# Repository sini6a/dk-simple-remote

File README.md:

# DK Simple Remote

A small BLE HID remote built around the WCH CH583, powered by a CR2032 cell.

| Folder / file | Contents |
|---|---|
| [`KiCad/`](KiCad/) | KiCad project `dk-simple-remote`: schematic, PCB, libraries, 3D models |
| `KiCad/production/` | Fabrication outputs (Gerbers, BOM, positions) |
| [`FreeCAD/`](FreeCAD/) | Enclosure |
| `Assets/` | Component datasheets |
| [`Firmware/`](Firmware/README.md) | Firmware source; the WCH SDK is a git submodule |

Clone with the SDK:

```sh
git clone --recurse-submodules <this-repo>
```

## License

This project uses two licenses:

- **Hardware** (everything outside `Firmware/`: the `KiCad/` project,
  fabrication outputs, enclosure and 3D models) is licensed under
  [Creative Commons Attribution-NonCommercial-ShareAlike 4.0](LICENSE)
  (CC BY-NC-SA 4.0). You may build, modify and share it for non-commercial
  purposes with attribution; derivatives must use the same license.
  Selling boards, kits or devices made from this design is not permitted.
- **Firmware** (`Firmware/`) is [MIT licensed](Firmware/LICENSE). WCH SDK
  components and WCH-derived files keep their Apache-2.0 terms; see
  [third-party notices](Firmware/THIRD_PARTY_NOTICES.md).

Datasheets in `Assets/` and vendor 3D models in `KiCad/Models/` belong to their
respective manufacturers and are not covered by either license.

Copyright (c) 2026 CH583 Remote contributors.

## Support

If you find this project useful, you can buy me a coffee:

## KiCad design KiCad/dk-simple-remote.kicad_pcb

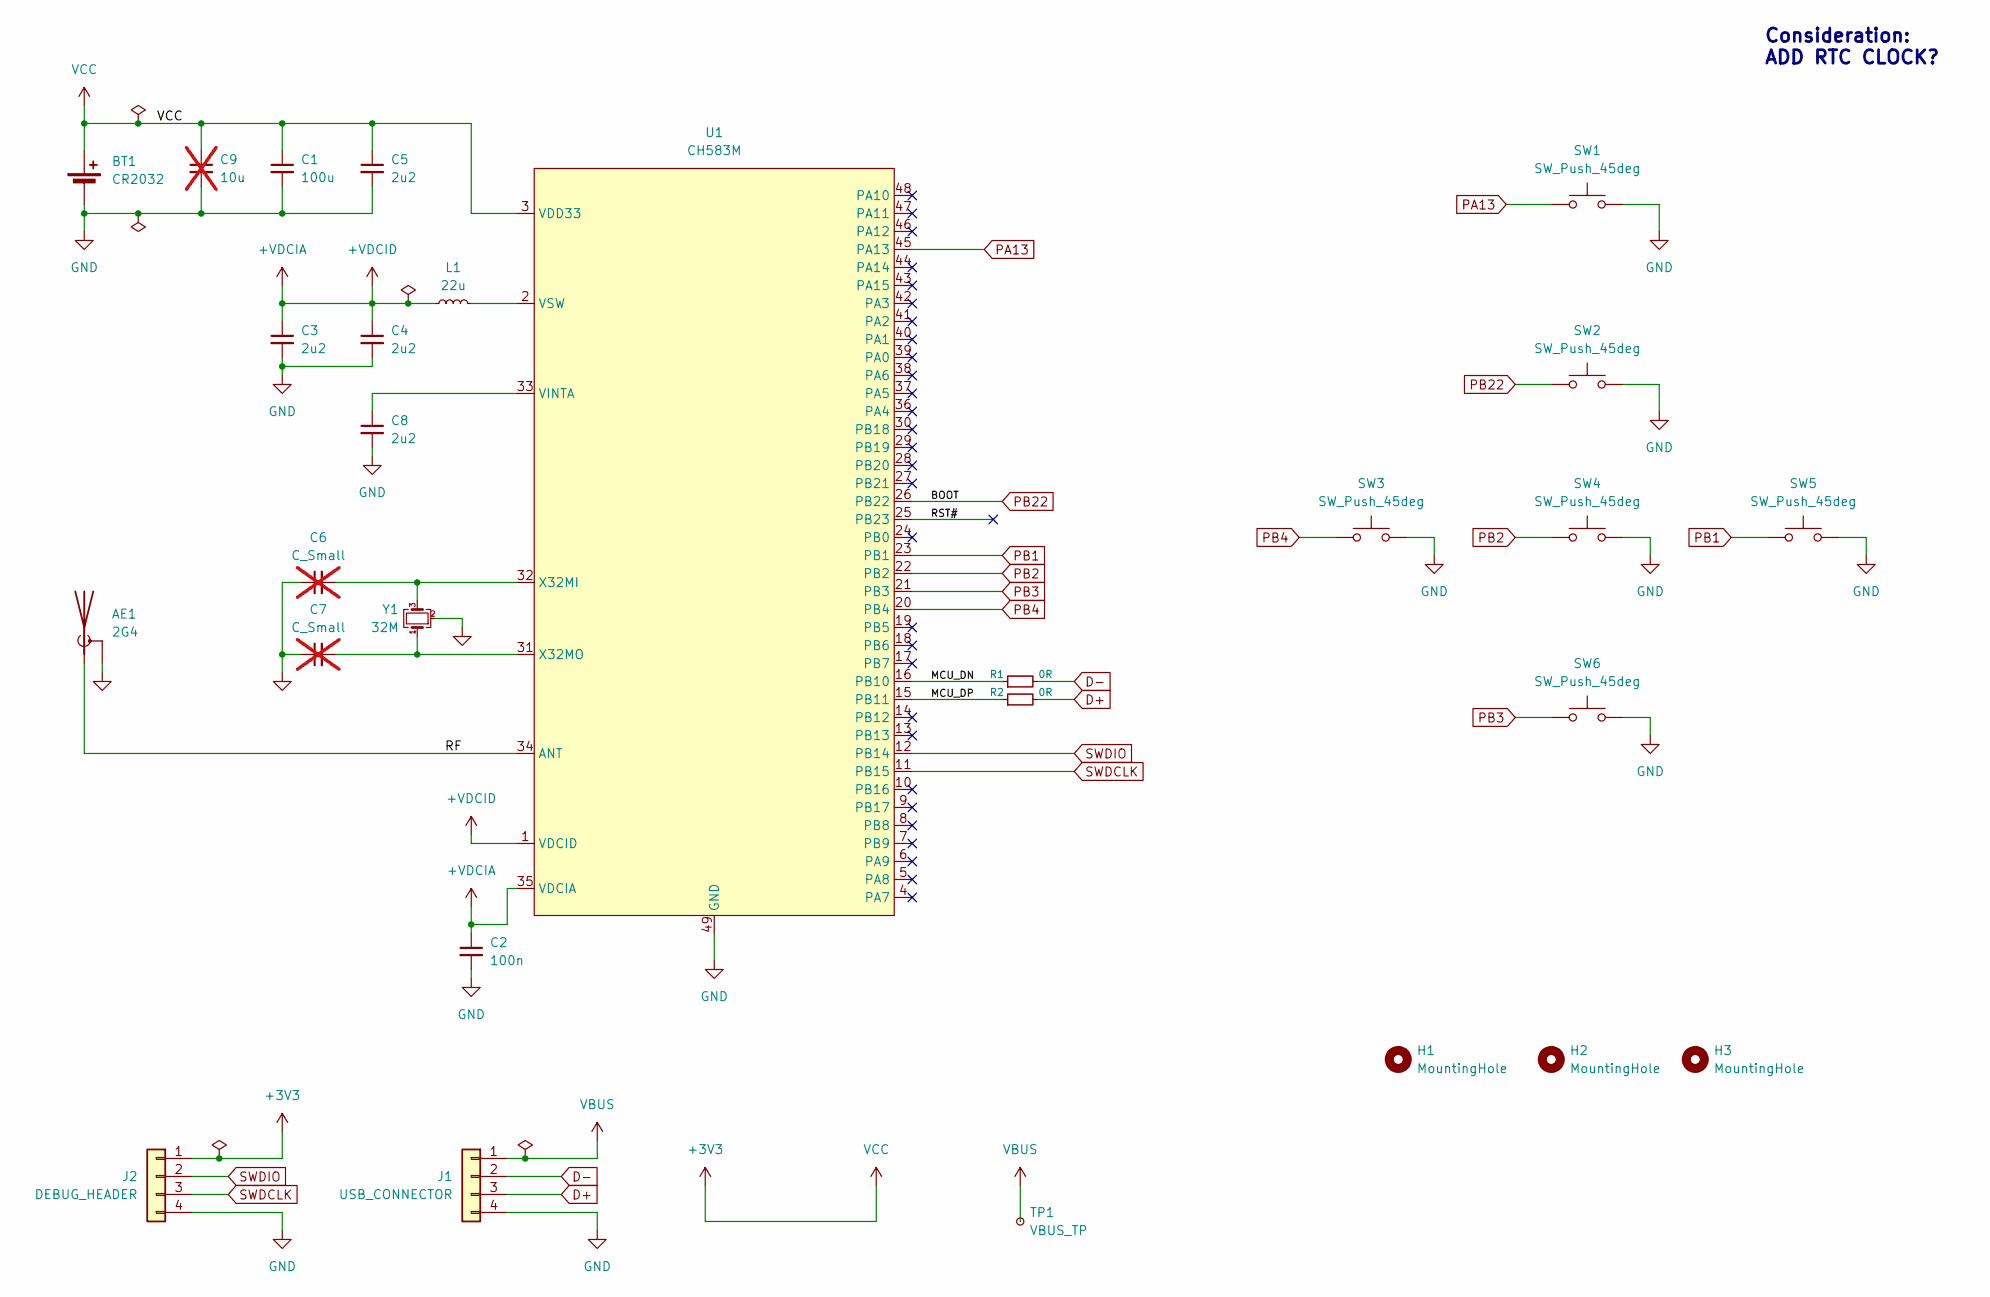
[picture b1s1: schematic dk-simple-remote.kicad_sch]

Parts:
AE1: 2G4; Texas_SWRA117D_2.4GHz_Left
BT1: CR2032; BatteryHolder_MPD_BC2003_1x2032
C1: 100u; C_1206_3216Metric; MPN C15008
C2: 100n; C_0402_1005Metric; MPN C1525
C3, C4, C5, C8: 2u2; C_0402_1005Metric; MPN C12530
C6, C7: C_Small; C_0402_1005Metric; not fitted
C9: 10u; C_0603_1608Metric; MPN C1713; not fitted
H1, H2, H3: MountingHole; MountingHole_3.2mm_M3_ISO14580
J1: USB_CONNECTOR; Hirose_DF13-04P-1.25DSA_1x04_P1.25mm_Vertical
J2: DEBUG_HEADER; Hirose_DF13-04P-1.25DSA_1x04_P1.25mm_Vertical
L1: 22u; L_APV_ANR3010; MPN C6364775
R1, R2: 0R; R_0402_1005Metric; MPN C17168
SW1, SW2, SW3, SW4, SW5, SW6: SW_Push_45deg; SW_Push_1P1T_NO_E-Switch_TL3301NxxxxxG; MPN C2837531
TP1: VBUS_TP; TestPoint_Pad_D1.5mm
U1: CH583M; QFN-48-1EP_5x5mm_P0.35mm_EP3.7x3.7mm
Y1: 32M; Crystal_SMD_2016-4Pin_2.0x1.6mm; MPN C383840

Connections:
+3V3: BT1.1 (+), C1.1, C5.1, C9.1, J2.1, U1.3 (VDD33)
+VDCIA: C2.1, C3.1, C4.1, L1.1, U1.1 (VDCID), U1.35 (VDCIA)
/MCU_DN: R1.1, U1.16 (PB10)
/MCU_DP: R2.1, U1.15 (PB11)
/RF: AE1.1 (A), U1.34 (ANT)
/RST#: U1.25 (PB23)
D+: J1.3, R2.2
D-: J1.2, R1.2
GND: AE1.2 (Shield), BT1.2 (-), C1.2, C2.2, C3.2, C4.2, C5.2, C6.1, C7.1, C8.2, C9.2, J1.4, J2.4, SW1.2, SW2.2, SW3.2, SW4.2, SW5.2, SW6.2, U1.49 (GND), Y1.2 (G), Y1.4 (G)
unnamed: C8.1, U1.33 (VINTA)
unnamed: L1.2, U1.2 (VSW)
unnamed: C6.2, U1.32 (X32MI), Y1.3
unnamed: C7.2, U1.31 (X32MO), Y1.1
PA13: SW1.1, U1.45 (PA13)
PB1: SW5.1, U1.23 (PB1)
PB2: SW4.1, U1.22 (PB2)
PB3: SW6.1, U1.21 (PB3)
PB4: SW3.1, U1.20 (PB4)
PB22: SW2.1, U1.26 (PB22)
SWDCLK: J2.3, U1.11 (PB15)
SWDIO: J2.2, U1.12 (PB14)
VBUS: J1.1, TP1.1 (1_1)

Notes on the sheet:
Consideration: ADD RTC CLOCK?

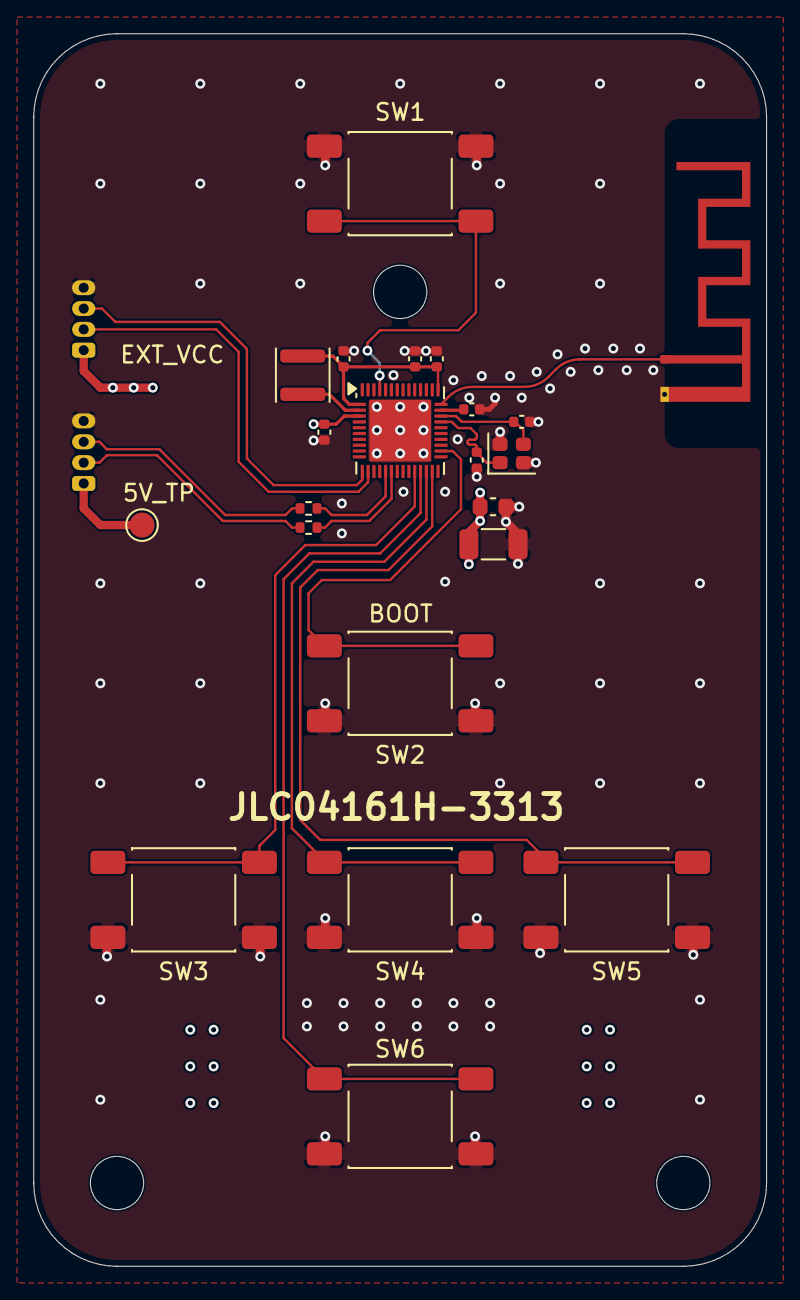
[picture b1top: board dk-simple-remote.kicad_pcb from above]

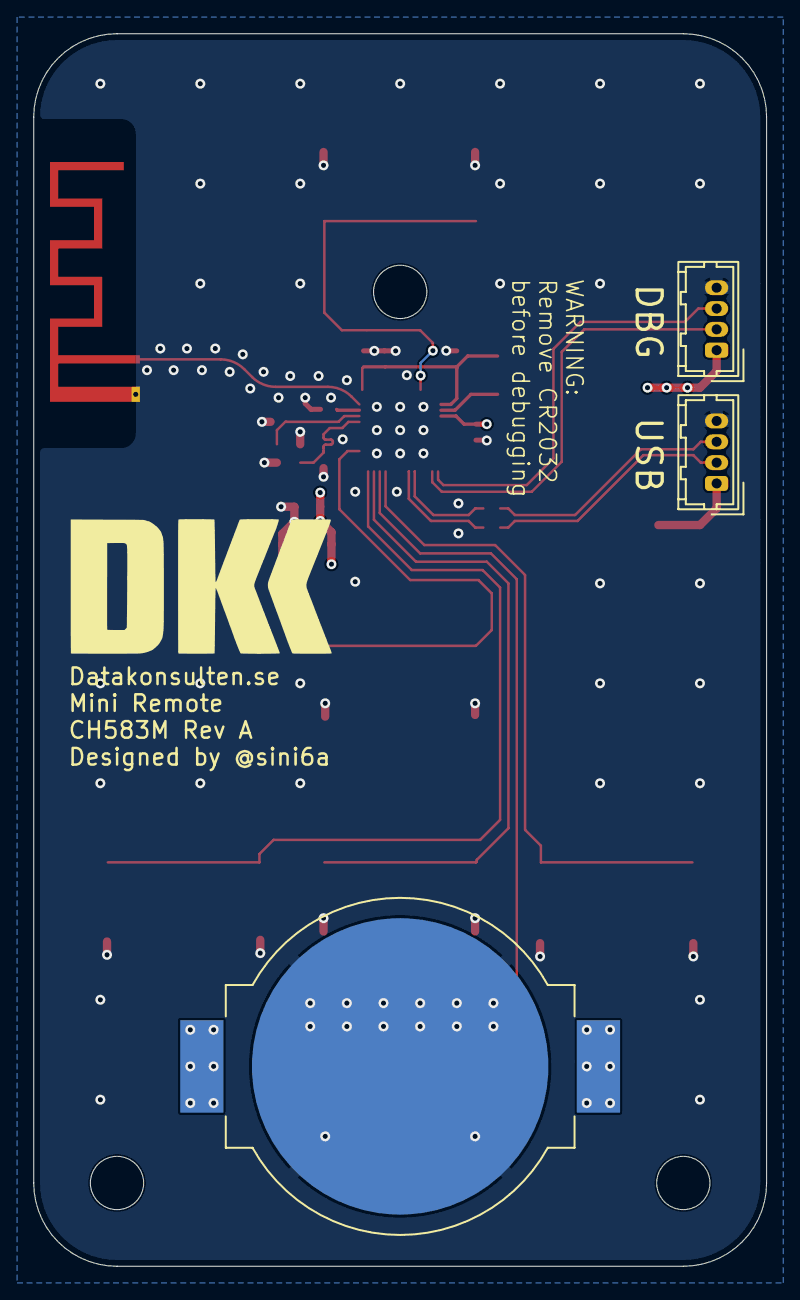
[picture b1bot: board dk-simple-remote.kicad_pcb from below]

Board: 4 copper layers, 44.0 x 74.0 mm, 28 parts (3 on the bottom side), 21 nets.

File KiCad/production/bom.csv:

Designator,Footprint,Quantity,Value,LCSC Part #
BT1,BatteryHolder_MPD_BC2003_1x2032,1,CR2032,
C1,0603,1,10u,C19702
C2,0402,1,100n,C1525
"C3, C4, C5, C8",0402,4,2u2,C12530
J1,Hirose_DF13-04P-1.25DSA_1x04_P1.25mm_Vertical,1,USB_CONNECTOR,
J2,Hirose_DF13-04P-1.25DSA_1x04_P1.25mm_Vertical,1,DEBUG_HEADER,
JP1,SolderJumper-2_P1.3mm_Open_RoundedPad1.0x1.5mm,1,RST#,
JP2,SolderJumper-2_P1.3mm_Open_RoundedPad1.0x1.5mm,1,BOOT,
L1,L_APV_ANR3010,1,22u,C6364775
"R1, R2",0402,2,0R,C17168
"SW1, SW2, SW3, SW4, SW5, SW6",SW_Push_1P1T_NO_E-Switch_TL3301NxxxxxG,6,SW_Push_45deg,C2837531
TP1,TestPoint_Pad_D1.5mm,1,VBUS_TP,
U1,QFN-48-1EP_5x5mm_P0.35mm_EP3.7x3.7mm,1,CH583M,
Y1,Crystal_SMD_2016-4Pin_2.0x1.6mm,1,32M,C141794

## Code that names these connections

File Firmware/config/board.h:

#ifndef REMOTE_BOARD_H
#define REMOTE_BOARD_H

/* CH583M QFN48: checked against CH583DS1_en.PDF and the KiCad PCB.
 * SW1 PA13/pad45, SW3 PB4/pad20, SW4 PB2/pad22, SW5 PB1/pad23,
 * SW6 PB3/pad21 on every revision. Active low. SW2 depends on BOARD_REV:
 *   rev1 (fabricated 2026-10-28): SW2 PB0/pad24; BOOT/RESET on jumpers JP2/JP1.
 *   rev2 (current PCB): SW2 PB22/pad26, the BOOT pin, so holding SW2 at
 *        power-up enters the WCH bootloader. JP1/JP2 removed.
 * Select with -DBOARD_REV=1 or 2 (tools/build.py --board rev1|rev2). */
#ifndef BOARD_REV
#define BOARD_REV 2
#endif
#define BOARD_BUTTON_A_MASK (1UL << 13)
#if BOARD_REV == 1
#define BOARD_SW2_PB_PIN 0U
/* GPIO port B pins: PB0-PB4. Interrupt bits are the same pins. */
#define BOARD_BUTTON_B_MASK 0x1FUL
#define BOARD_BUTTON_B_INT_MASK 0x1FUL
#define BOARD_SW2_INT_REMAP 0
#elif BOARD_REV == 2
#define BOARD_SW2_PB_PIN 22U
/* GPIO port B pins (R32_PB_* registers): PB22 and PB1-PB4. */
#define BOARD_BUTTON_B_MASK ((1UL << 22) | 0x1EUL)
/* Same pins in the 16-bit R16_PB_INT_* registers. PB22 uses interrupt bit 8
 * once RB_PIN_INTX remaps INT24 from PB8 (unconnected) to PB22. */
#define BOARD_BUTTON_B_INT_MASK ((1UL << 8) | 0x1EUL)
#define BOARD_SW2_INT_REMAP 1
#else
#error "BOARD_REV must be 1 or 2"
#endif
#define BOARD_DCDC_INDUCTOR_UH 22
/* User-confirmed Y1: YXC X201632MMB4SI, CL=10pF; C6/C7 not fitted.
 * Reported 4pF stray is an estimate, not a measured tuning parameter.
 * Keep SDK oscillator tuning unchanged while testing the HID latency fix. */
/* Preserve PB10/11 USB, PB14/15 debug, PB22/23 BOOT/reset (PB22 is SW2 on rev2),
 * PB8 (its interrupt is remapped on rev2),
 * PA10/11 possible 32k pins, and all RF/clock/power pins. */
#endif
